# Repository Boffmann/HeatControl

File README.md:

# HeatControl

Simple script to run on a Raspberry Pi in order to control the temperature in a closed environment. Features a web application to monitor and control the system.

# Components

Features:

* **Raspberry Pi**
  Runs script to reads out sensor data and perform required actions. I'm using a Raspberry Pi 1.
* **Custom Shield**
  A custom shield for the Pi used to connect all components. For more details see the section below.
* **Heater**
  The heater is activated when the temperature drops to low. The heater I applied here is a [300W Heater](https://www.amazon.de/Keramisches-Luftheizelement-Thermostat-PTC-isolierte-elektrische/dp/B07MDCMFCQ/ref=sr_1_1_sspa?keywords=keramisches+luftheizelement&qid=1643123726&sprefix=keramisches+lufthei%2Caps%2C72&sr=8-1-spons&psc=1&smid=A2QDVE2OGM9E0I&spLa=ZW5jcnlwdGVkUXVhbGlmaWVyPUE2NU03NUxQTkpDNjYmZW5jcnlwdGVkSWQ9QTAwNDQ4NTAzTlVOTTRTSFgwSThKJmVuY3J5cHRlZEFkSWQ9QTA0MTY1ODUyV0pQTDlTN1JSTlZKJndpZGdldE5hbWU9c3BfYXRmJmFjdGlvbj1jbGlja1JlZGlyZWN0JmRvTm90TG9nQ2xpY2s9dHJ1ZQ==).
* **Fan**
  Provides air circulation to distribute the heat. I'm using a 24V casing fan.
* **Temperature Sensors**
  Used to sense the environment temparature. I'm using two [DS18B20](https://www.amazon.de/AZDelivery-digitaler-Temperatursensor-Temperaturf%C3%BChler-wasserdicht/dp/B07KNQJ3D7/ref=sr_1_1_sspa?__mk_de_DE=%C3%85M%C3%85%C5%BD%C3%95%C3%91&crid=2U0ZHPSJCCDZD&keywords=DS18B20&qid=1643123820&sprefix=ds18b20%2Caps%2C78&sr=8-1-spons&psc=1&smid=A1X7QLRQH87QA3&spLa=ZW5jcnlwdGVkUXVhbGlmaWVyPUExNDlRUkUyWU9RNUZYJmVuY3J5cHRlZElkPUEwODYwNjA4OFhCTVM5VTdLSTUmZW5jcnlwdGVkQWRJZD1BMDYyODIzMDJUOEJXR0dNRUsyV1Imd2lkZ2V0TmFtZT1zcF9hdGYmYWN0aW9uPWNsaWNrUmVkaXJlY3QmZG9Ob3RMb2dDbGljaz10cnVl5) temperature sensors in this project and calculate temperature by deriving the mean value of both sensors.

## Custom Shield

The final soldered shield.

TODO
The shield's circuit.

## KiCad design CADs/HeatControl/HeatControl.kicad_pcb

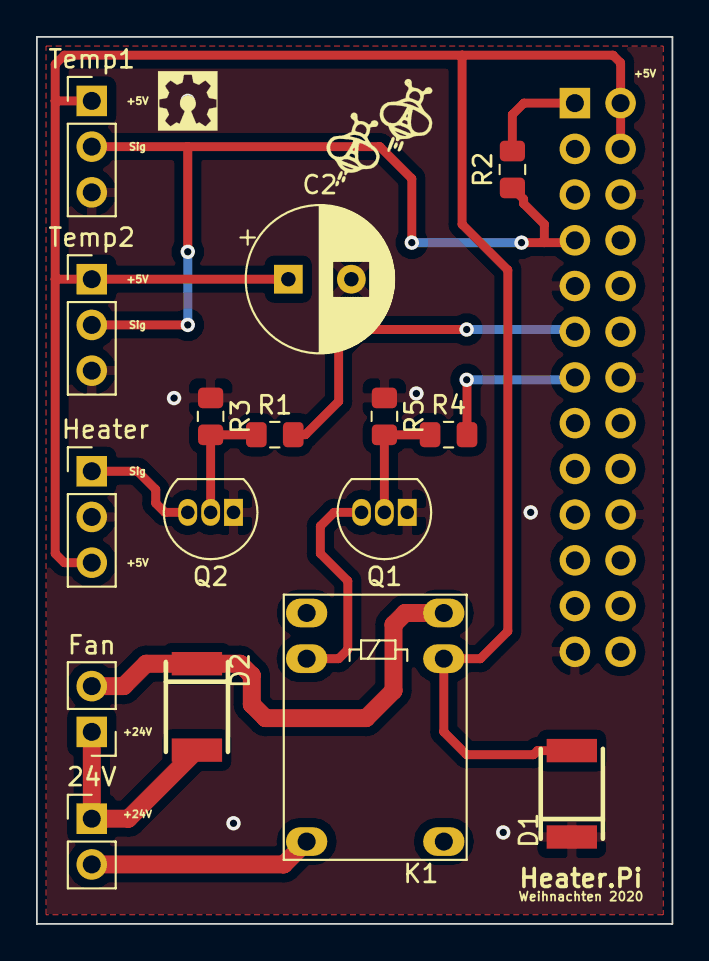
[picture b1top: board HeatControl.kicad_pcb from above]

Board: 2 copper layers, 35.3 x 49.3 mm, 16 parts (0 on the bottom side), 10 nets.

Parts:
24V: 24VPins; PinHeader_1x02_P2.54mm_Vertical
C2: 100µF; CP_Radial_D8.0mm_P3.50mm
D1, D2: 1N4001; DO-213AB
Fan: Fan; PinHeader_1x02_P2.54mm_Vertical
Heater: 240VRelais; PinHeader_1x03_P2.54mm_Vertical
K1: TIANBO-HJR-4102-L; Relay_SPDT_HJR-4102
Q1, Q2: 2N2219; TO-92_Inline
R1, R4: 470; R_0805_2012Metric_Pad1.15x1.40mm_HandSolder
R2, R3: 4.7K; R_0805_2012Metric_Pad1.15x1.40mm_HandSolder
R5: 4,7K; R_0805_2012Metric_Pad1.15x1.40mm_HandSolder
Temp1: Temp_Sensor; PinHeader_1x03_P2.54mm_Vertical
Temp2: TempSensor; PinHeader_1x03_P2.54mm_Vertical

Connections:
+5V: C2.1, D1.1, Heater.3, K1.5, Temp1.1, Temp2.1
+24V: 24V.1, D2.1, Fan.1
/24VGND: 24V.2, K1.12
/TempData: R2.1, Temp1.2, Temp2.2
GND: C2.2, D1.2, Heater.2, Q1.1, Q2.1, R3.1, R5.1, Temp1.3, Temp2.3
unnamed: Heater.1, Q2.3
unnamed: D2.2, Fan.2, K1.6
unnamed: K1.8, Q1.3
unnamed: Q1.2, R4.1, R5.2
unnamed: Q2.2, R1.1, R3.2

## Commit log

2020-12-14 First version readme
2020-12-14 Multiprocessing and flask
2020-12-14 Update temp should in frontend
2020-12-14 Update tempis in frontend
2020-12-15 Add Raspi interface in code
2020-12-15 Add css
2020-12-15 Reflect onoff in background color
2020-12-15 Make better sync
2020-12-15 indention
2020-12-16 Error handling
2020-12-17 Temp to double and remove upperlimit
2020-12-17 Add route for current temps
2020-12-18 Width height vh vw
2020-12-18 Fix conversion
2020-12-18 round to two
2020-12-18 set up interval time
2020-12-18 Add tolerance again
2020-12-18 Some small changes
2020-12-18 Show in frontend if heating
2020-12-18 Turn off heating when starting
2020-12-18 Add heater script
2020-12-18 Rework start script
2020-12-22 Add CAD Board files
2020-12-22 Update board
2020-12-25 Board rework
2020-12-27 Finalize board - Ordered
2020-12-28 Add logger
2020-12-28 Add config as yaml
2020-12-28 Add board outline
2020-12-28 Refactoring state and superviser
2020-12-28 Glue server and superviser process together
2020-12-28 Add database connection
2020-12-29 Do ajax stuff with websockets
2020-12-29 Connect to socket in superviser to publish temp_is
2020-12-29 Add new temp values to database in history socket
2020-12-29 Provide database data and new data to history page
2020-12-30 Fit entire view on one screen
2020-12-30 Add charts
2020-12-30 Add navbar
2021-01-03 Rewrite Heatcontrol for new interface
2021-01-03 Add function to calculate how long to heat
2021-01-03 Implement state machine
2021-01-03 Reworked logging
2021-01-03 Inform about changes in heating variable
2021-01-03 Show time on graph in day and time
2021-01-03 Force size of graph
2021-01-03 Max ticks in graph gleich 30
2021-01-04 Add temp should to db and graph
2021-01-04 Only turn something on when actually running
2021-01-12 Enable RasPi Interface
2021-01-24 Make changes for raspi
2021-01-25 Should fix bug that fan not turned off
2022-01-26 Creates first version of simple start/stop gui
2022-01-26 styling and error handling in gui
2022-01-27 Restructuring
2022-01-27 Centralize rounding to two digits after comma
2022-01-27 Rename src directory to heatcontrol
2022-01-27 Adds template ssh config
2022-01-27 Adds scripts that are invoked by GUI
2022-01-28 Error handling in GUI
2022-02-01 Adds test state
2022-02-01 Connect properly to socket in state
